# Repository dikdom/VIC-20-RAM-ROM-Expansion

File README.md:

# VIC-20-RAM-ROM-Expansion
Commodore VIC-20 RAM and ROM expansion module

This is a low cost memory expansion module for the Commodore VIC-20 machine. The module is capable of expanding the RAM1, RAM2, RAM3 and BLK1, BLK2, BLK3 and BLK5 memory areas. Altogether 35kB of RAM expansion, manually switchable way.

The module can host an AT28C256 32kB EEPROM chip also, containing 4x 8kB of ROM image mapped to BLK5. BLK5 is selectable: it can be either RAM (has to be enabled on the DIP switch) or can be ROM (DIP switch doesn't play any role).

BOM:
- 10k, 9+1 resistor bridge, SIL10
- 10k, 3# normal resistor
- 3pcs of 100nF, 1# ceramic capacitor (at least 5V, 50V is just fine)
- 22uF, 1# electrolythic capacitor (at lest 5V, 16V/25V is just fine),
- DIP switch, with 10 switches (3#)
- 74LS148, DIP-16 (+ optionally socket)
- 628128 RAM, 128kB, DIP-32 (+ optionally socket)
- 3 pin header + jumper

OPTIONAL
- AT28C256, 32kB EEPROM. Each 8kB bank shall contain an 8kB VIC20 cartridge program which is mapped to $A000-$BFFF (Block 5)
- Tactile push button for RESET

# Usage
The jumper can select what shall the VIC20 see on BLK5: ROM or RAM. If not used, then BLK5 will be unpopulated in VIC20. 
The DIP swithches 1-3 can turn on/off the RAM1/RAM2/RAM3 expansion (1kB each). The DIP switches 4-7 can turn on/off the BLK1,BLK2,BLK3,BLK5 RAM expansions (8kB each).
In case ROM is selected with the jumper, then DIP switches 9-10 can select the 8kB ROM bank from the EEPROM.
The DIP switch 8 is not used. 

# Directories
- eagle

  The Eagle design files (schematics and board plans and necessary libraries)

- doc

  Schematics, board in visible form (pdf) and the gerber file package.

# License #

Creative Commons License

This work is licensed under [Creative Commons Attribution-NonCommercial-ShareAlike 4.0 International License](https://creativecommons.org/licenses/by-nc-sa/4.0/).

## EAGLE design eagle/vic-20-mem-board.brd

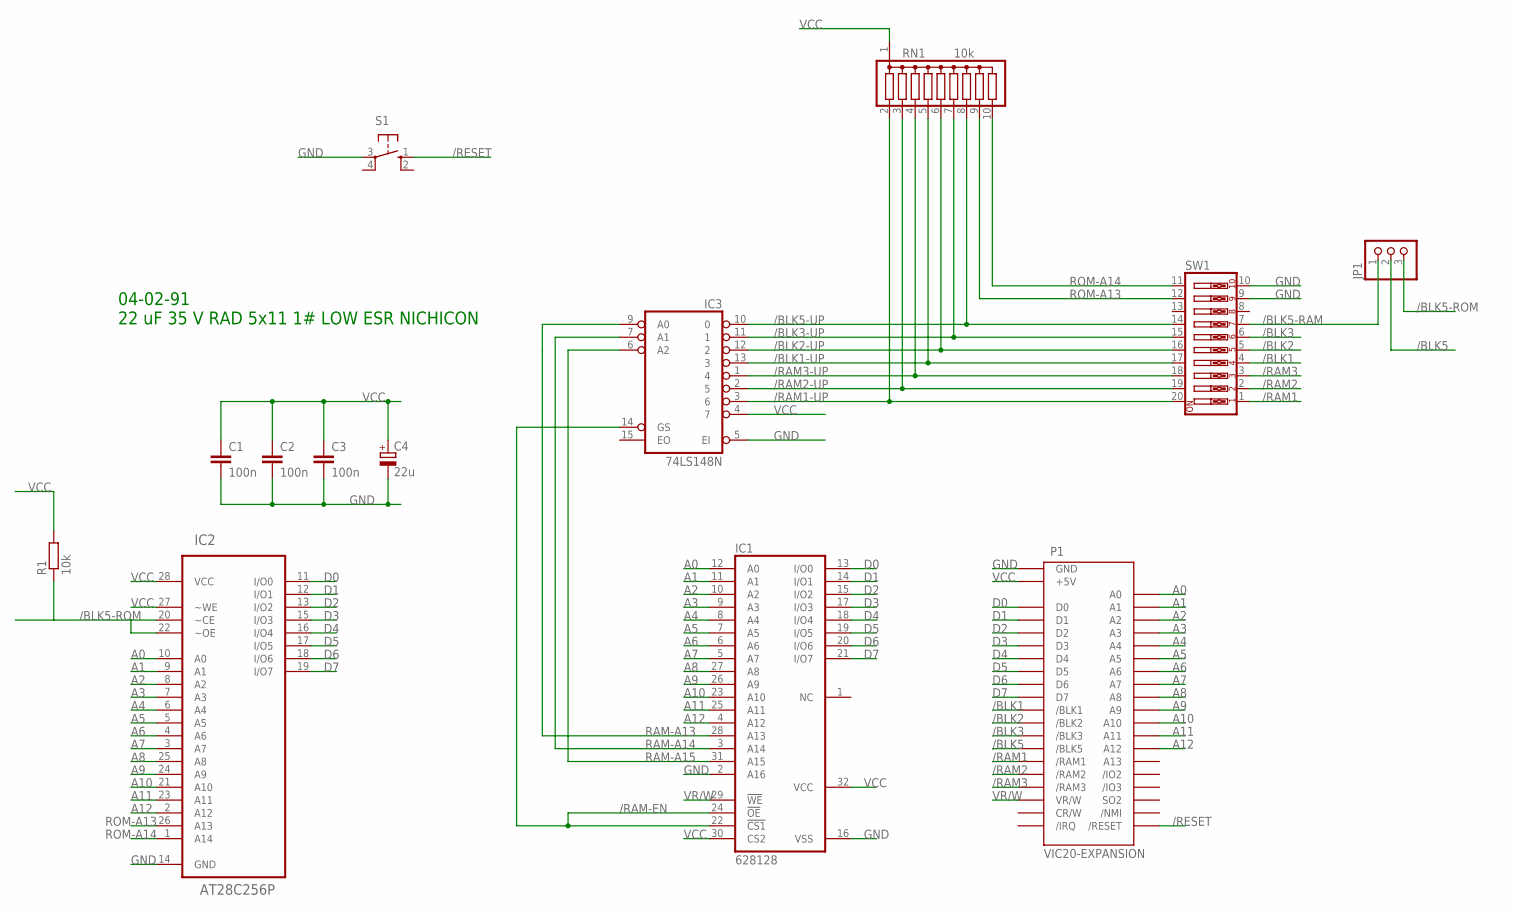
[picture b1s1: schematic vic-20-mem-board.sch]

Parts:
C1, C2, C3: 100n; C025-025X050
C4: 22u; E2,5-5
IC1: 628128; DIL32
IC2: AT28C256P; DIL28-6
IC3: 74LS148N; DIL16
JP1: PINHD-1X3; 1X03
P1: VIC20-EXPANSION; 44PINEDGE
R1: 10k; 0204/7
RN1: 10k; SIL10
S1: 10-XX; B3F-10XX
SW1: SW_DIP-10; EDG-10

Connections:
/BLK1: P1.10 (/BLK1), SW1.4
/BLK1-UP: IC3.13 (3), RN1.5, SW1.17
/BLK2: P1.11 (/BLK2), SW1.5
/BLK2-UP: IC3.12 (2), RN1.6, SW1.16
/BLK3: P1.12 (/BLK3), SW1.6
/BLK3-UP: IC3.11 (1), RN1.7, SW1.15
/BLK5: JP1.2, P1.13 (/BLK5)
/BLK5-RAM: JP1.1, SW1.7
/BLK5-ROM: IC2.20 (~CE), IC2.22 (~OE), JP1.3, R1.1
/BLK5-UP: IC3.10 (0), RN1.8, SW1.14
/RAM1: P1.14 (/RAM1), SW1.1
/RAM1-UP: IC3.3 (6), RN1.2, SW1.20
/RAM2: P1.15 (/RAM2), SW1.2
/RAM2-UP: IC3.2 (5), RN1.3, SW1.19
/RAM3: P1.16 (/RAM3), SW1.3
/RAM3-UP: IC3.1 (4), RN1.4, SW1.18
/RAM-EN: IC1.22 (!CS1), IC1.24 (!OE), IC3.14 (GS)
/RESET: P1.X (/RESET), S1.1 (S)
A0: IC1.12 (A0), IC2.10 (A0), P1.B (A0)
A1: IC1.11 (A1), IC2.9 (A1), P1.C (A1)
A2: IC1.10 (A2), IC2.8 (A2), P1.D (A2)
A3: IC1.9 (A3), IC2.7 (A3), P1.E (A3)
A4: IC1.8 (A4), IC2.6 (A4), P1.F (A4)
A5: IC1.7 (A5), IC2.5 (A5), P1.H (A5)
A6: IC1.6 (A6), IC2.4 (A6), P1.J (A6)
A7: IC1.5 (A7), IC2.3 (A7), P1.K (A7)
A8: IC1.27 (A8), IC2.25 (A8), P1.L (A8)
A9: IC1.26 (A9), IC2.24 (A9), P1.M (A9)
A10: IC1.23 (A10), IC2.21 (A10), P1.N (A10)
A11: IC1.25 (A11), IC2.23 (A11), P1.P (A11)
A12: IC1.4 (A12), IC2.2 (A12), P1.R (A12)
D0: IC1.13 (I/O0), IC2.11 (I/O0), P1.2 (D0)
D1: IC1.14 (I/O1), IC2.12 (I/O1), P1.3 (D1)
D2: IC1.15 (I/O2), IC2.13 (I/O2), P1.4 (D2)
D3: IC1.17 (I/O3), IC2.15 (I/O3), P1.5 (D3)
D4: IC1.18 (I/O4), IC2.16 (I/O4), P1.6 (D4)
D5: IC1.19 (I/O5), IC2.17 (I/O5), P1.7 (D5)
D6: IC1.20 (I/O6), IC2.18 (I/O6), P1.8 (D6)
D7: IC1.21 (I/O7), IC2.19 (I/O7), P1.9 (D7)
GND: C1.2, C2.2, C3.2, C4.-, IC1.2 (A16), IC1.16 (VSS), IC2.14 (GND), IC3.5 (EI), IC3.8 (GND), P1.1 (GND), P1.22 (GND), P1.A (GND), P1.Z (GND), S1.3, SW1.9, SW1.10
RAM-A13: IC1.28 (A13), IC3.9 (A0)
RAM-A14: IC1.3 (A14), IC3.7 (A1)
RAM-A15: IC1.31 (A15), IC3.6 (A2)
ROM-A13: IC2.26 (A13), RN1.9, SW1.12
ROM-A14: IC2.1 (A14), RN1.10, SW1.11
VCC: C1.1, C2.1, C3.1, C4.+, IC1.30 (CS2), IC1.32 (VCC), IC2.27 (~WE), IC2.28 (VCC), IC3.4 (7), IC3.16 (VCC), P1.21 (+5V), R1.2, RN1.1
VR/W: IC1.29 (!WE), P1.17 (VR/W)

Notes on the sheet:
04-02-91 22 uF 35 V RAD 5x11 1# LOW ESR NICHICON

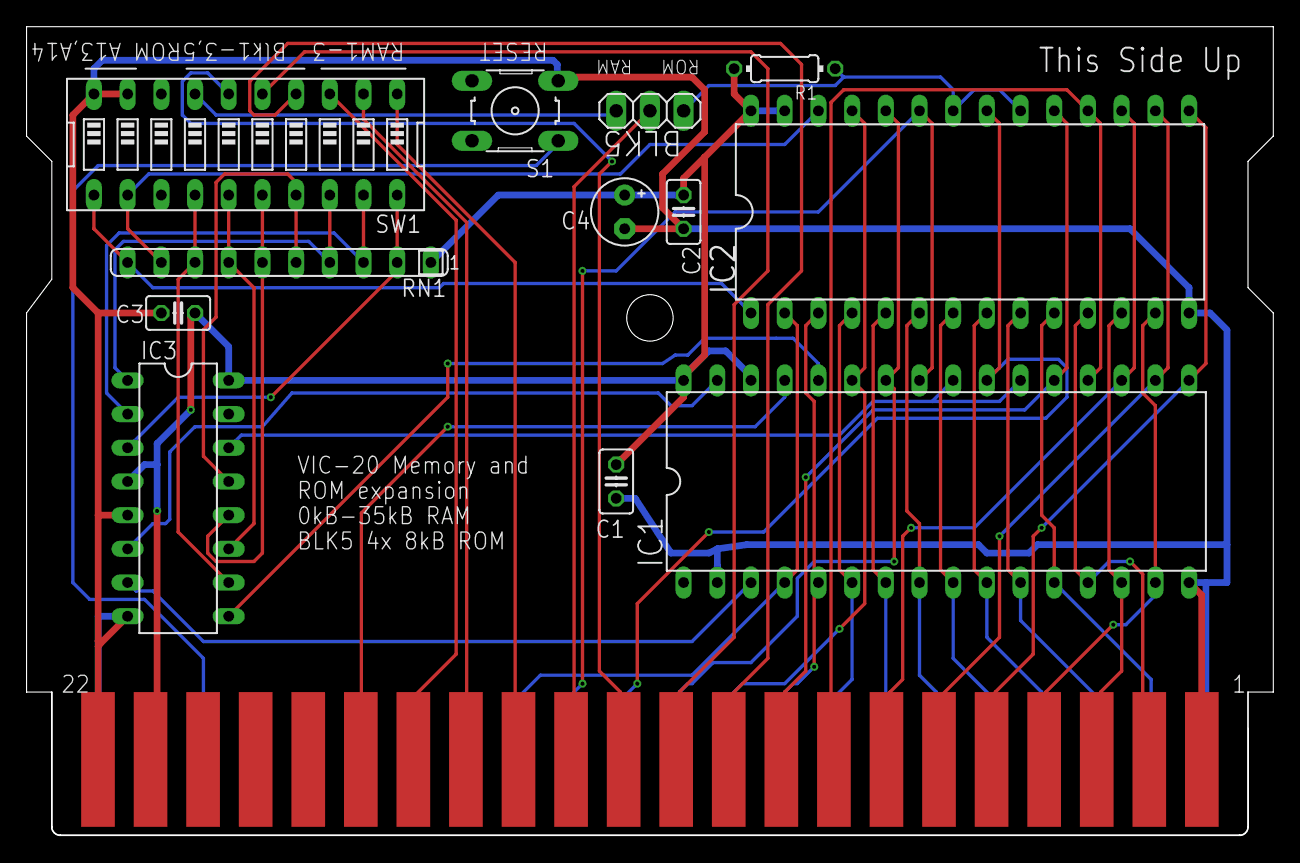
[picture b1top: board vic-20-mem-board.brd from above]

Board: 2 copper layers, 93.9 x 60.9 mm, 13 parts (0 on the bottom side), 47 nets.

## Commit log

2019-10-27 Update README.md
    typos fixed..
